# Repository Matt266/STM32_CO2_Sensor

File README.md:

# STM32_CO2_Sensor
KiCAD files and Arduino Code for SCD41 based CO2 Sensor

Most important parts:  
  -STM32L051K  
  -SCD41 (Sensor)  
  -Waveshare 1.54 inch e-Paper (V2)  
  -STLink-V2 (for programming)  

*Complete PCB with display showing measurements*

*Closer view to the PCB*

## The Hardware
The CO2 Sensor uses a Waveshare 1.54 Inch e-Paper (V2 Version) to display CO2, temperature and humidity measurements.
After creating a simple test device with an CCS811 Sensor and an Arduino Nano I wanted to create a working device.
This test device had two main issues I wanted to address: A high current consumption (50mA) and wrong measurement values
due to the cheap Sensor used.

For this I changed quite a few things. I changed the I2C-Oled Display for an e-Paper which reduces standby current consumption
but also decreases the display refresh rate. As the new more precise Sensor (SCD41) offers an one shot mode (SCD40 only got a
periodic measurement mode) the decreased refresh rate isn't a problem - measurements are only taken every few minutes.
Instead of an Arduino Board I designed a custom board. With that I could ditch the AVR MCU for a low power STM32L051. The 
PCB was designed for a STM32L011 but I underestimated the RAM and FLASH usage of code. I only got STM32L051 due to chip shortage
but would have had to "upgrade" to those anyways. I dropped the voltage level to 2.8V to make battery powering easier.

Indeed I managed to decrease the average current consumption to less than 1mA with larger spikes during measurements.

## The Software
At first I wanted to write the code with only the cmsis library but since getting all hardware components already took me months
mainly because the most important part - the MCU - wasn't available I switched to a faster method of writing code: Arduino IDE
For all features I needed there were libraries (near to) ready to use which probably cut developement time by more than a month.

I only had to do some changes to the e-Paper library (https://github.com/SSYYL/e-Paper): 
Since I didn't use the AVR I had to replace the PROGMEM calls and AVR specific libaries. In ARM based projects constant
values are stored in flash memory without special keywords anyways (linkerscript magic :D)
`
const uint8_t Font12_Table[] PROGMEM
`

There was also an AVR inline assembly call which I replaced even though it didn't seem to cause problems.

The Arduino Code itself is relatively simple: A small startup sequence configures and tests the sensor as well as
initializes the e-Paper. After that every 5 minutes a single shot measurement is taken. For simplicity I utilized
the busy waiting that was already implemented in the CO2-Library while waiting for the measurement data.
After recieving the data strings are formatted for printing them on the e-Paper. The red, yellow and green LEDs
are switched on/off based on CO2 threshold values. After displaying the new data on the display low power sleep 
is entered for 5min before taking the next measurement. Averaging algorithms are not needed as the Sensor itself
uses a sophisticated algorithm to calculate the CO2-ppm-value.

## The Problems
Sadly in DIY projects things can go wrong and some things went wrong in this project too.

First of all I somehow managed to mislabel the unused PINs which isn't fixed in the KiCAD files yet.
The next problem was that I couldn't get reliable connections soldering the Sensor to the PCB directly.
As the solder joints can't be seen after soldering I could never know if I all joints were good. 
After some weeks of seemingly random errors I used wires to solder the sensor to the PCB. It may not look
good or professional but at least works reliable.
The last and most expensive thing I did wrong killed the sensor and some Pins on the MCU. 
For debbuging purposes I used an STM32 evaluation board and connected to the I2C header of the PCB and
reading the serial monitor.
After finally getting a MCU I tried to test the same code with the STM32L051. I didn't turn off the serial
messages. As the standard UART on STML051 uses the same PINs as I2C on STM32L011 those were directly connected
to the sensors I2C pins. Thus sending a serial message lead to a short circuit resulting in a dead sensor and
fried PINs on the MCU.

## Future Plans
As of the state of writing the PCB is powered by a 2.8V LDO. For making it battery powered a boost converter
will be added on a seperate PCB. Also after adding the boost converter an enclosure to protect everything will
be made.

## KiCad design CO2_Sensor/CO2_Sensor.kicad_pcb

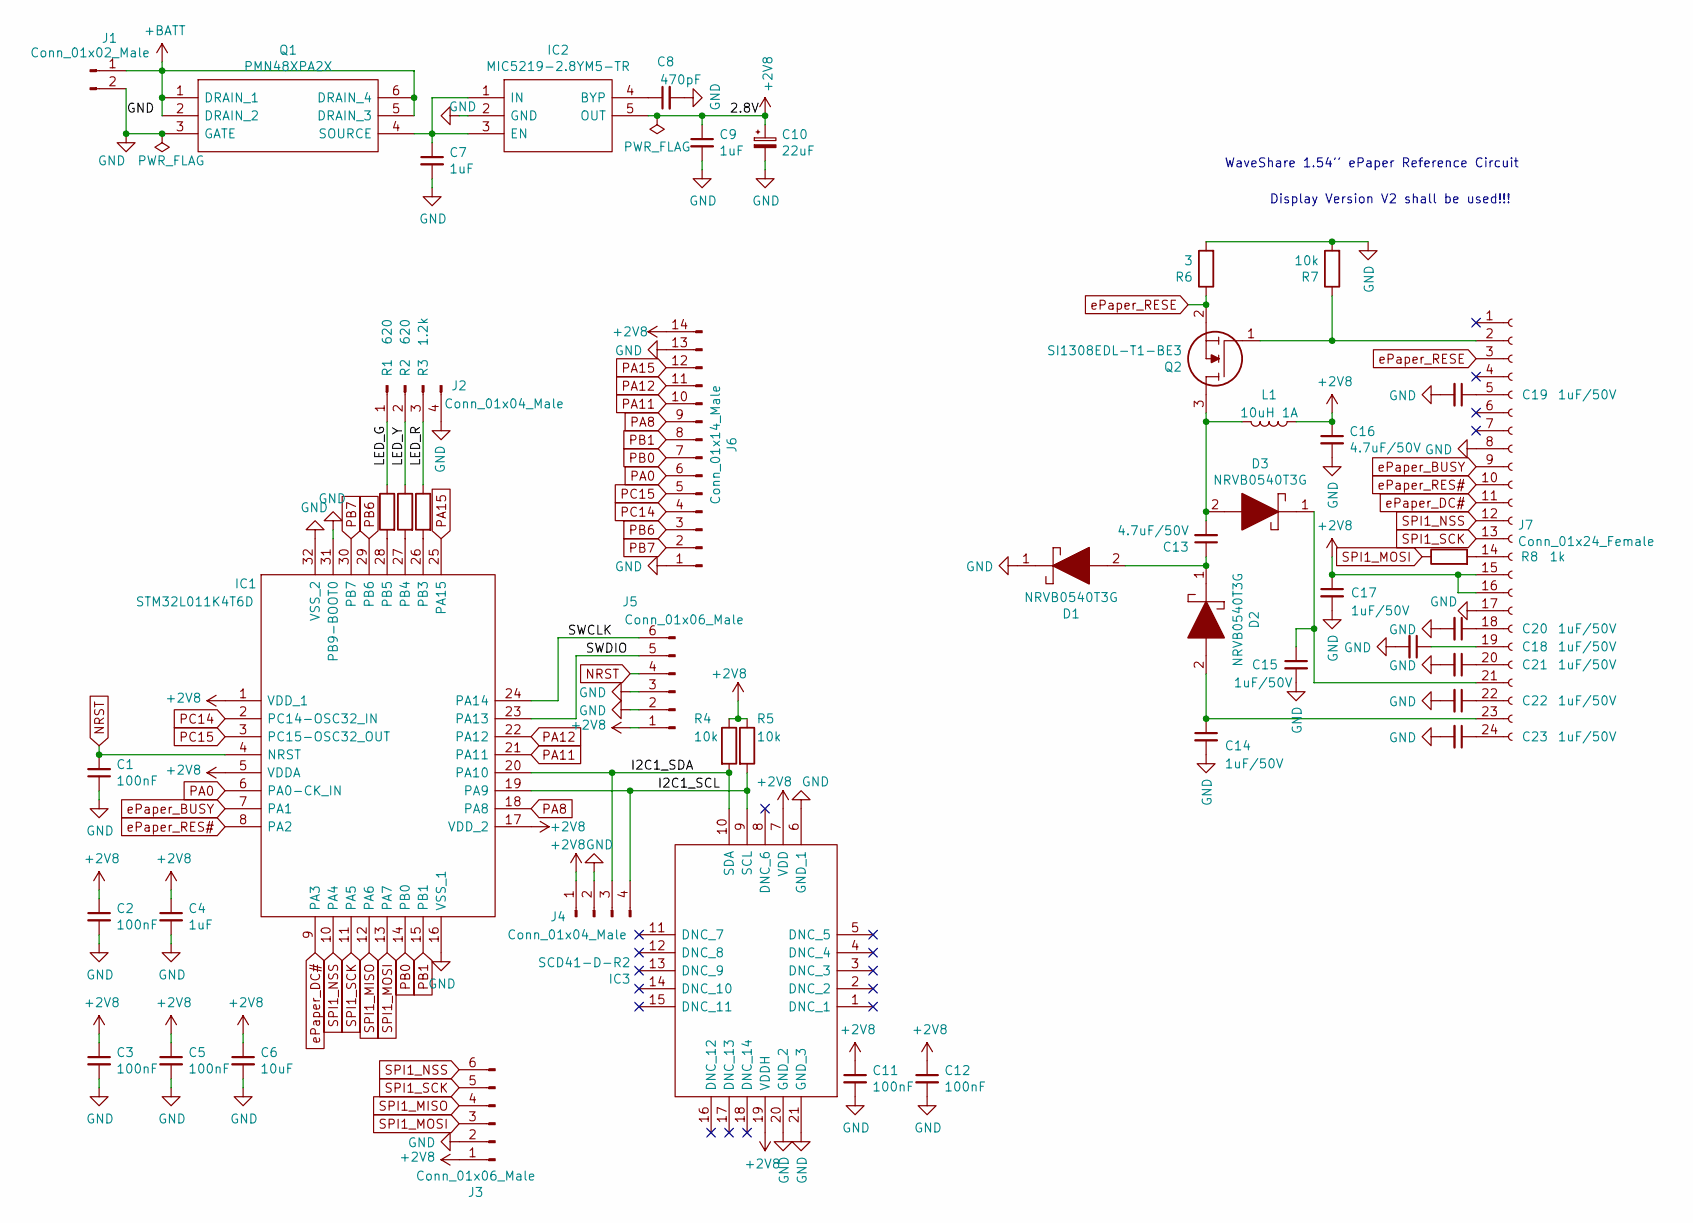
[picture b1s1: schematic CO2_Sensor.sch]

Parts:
C1, C2, C3, C5, C11, C12: 100nF; C_0805_2012Metric_Pad1.18x1.45mm_HandSolder
C4, C7, C9: 1uF; C_0805_2012Metric_Pad1.18x1.45mm_HandSolder
C6: 10uF; C_0805_2012Metric_Pad1.18x1.45mm_HandSolder
C8: 470pF; C_0805_2012Metric_Pad1.18x1.45mm_HandSolder
C10: 22uF; CP_Elec_4x5.4
C13, C16: 4.7uF/50V; C_0805_2012Metric_Pad1.18x1.45mm_HandSolder
C14, C15, C17, C18, C19, C20, C21, C22, C23: 1uF/50V; C_0805_2012Metric_Pad1.18x1.45mm_HandSolder
D1, D2, D3: NRVB0540T3G; SOD3716X135N; Mouser Part Number 863-NRVB0540T3G
IC1: STM32L011K4T6D; QFP80P900X900X160-32N; Mouser Part Number 511-STM32L011K4T6D
IC2: MIC5219-2.8YM5-TR; SOT95P280X145-5N; Mouser Part Number 998-MIC5219-2.8YM5TR
IC3: SCD41-D-R2; SCD41DR2; Mouser Part Number 403-SCD41-D-R2
J1: Conn_01x02_Male; PinSocket_1x02_P2.54mm_Vertical
J2, J4: Conn_01x04_Male; PinSocket_1x04_P2.54mm_Vertical
J3, J5: Conn_01x06_Male; PinSocket_1x06_P2.54mm_Vertical
J6: Conn_01x14_Male; PinSocket_1x14_P2.54mm_Vertical
J7: Conn_01x24_Female; TE_2-1734839-4_1x24-1MP_P0.5mm_Horizontal
L1: 10uH 1A; L_0805_2012Metric_Pad1.05x1.20mm_HandSolder
Q1: PMN48XPA2X; SOT95P275X110-6N; Mouser Part Number 771-PMN48XPA2X
Q2: SI1308EDL-T1-BE3; SOT65P210X110-3N; Mouser Part Number 78-SI1308EDL-T1-BE3
R1, R2: 620; R_0805_2012Metric_Pad1.20x1.40mm_HandSolder
R3: 1.2k; R_0805_2012Metric_Pad1.20x1.40mm_HandSolder
R4, R5, R7: 10k; R_0805_2012Metric_Pad1.20x1.40mm_HandSolder
R6: 3; R_0805_2012Metric_Pad1.20x1.40mm_HandSolder
R8: 1k; R_0805_2012Metric_Pad1.20x1.40mm_HandSolder

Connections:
+2V8: C2.1, C3.1, C4.1, C5.1, C6.1, C9.1, C10.1, C11.1, C12.1, C16.1, C17.1, IC1.1 (VDD_1), IC1.5 (VDDA), IC1.17 (VDD_2), IC2.5 (OUT), IC3.7 (VDD), IC3.19 (VDDH), J3.1, J4.1, J5.1, J6.14, J7.15, J7.16, L1.1, R4.1, R5.1
+BATT: J1.1, Q1.1 (DRAIN_1), Q1.2 (DRAIN_2), Q1.5 (DRAIN_3), Q1.6 (DRAIN_4)
/I2C1_SCL: IC1.19 (PA9), IC3.9 (SCL), J4.4, R5.2
/I2C1_SDA: IC1.20 (PA10), IC3.10 (SDA), J4.3, R4.2
/LED_G: J2.1, R1.1
/LED_R: J2.3, R3.1
/LED_Y: J2.2, R2.1
/SWCLK: IC1.24 (PA14), J5.6
/SWDIO: IC1.23 (PA13), J5.5
GND: C1.1, C2.2, C3.2, C4.2, C5.2, C6.2, C7.2, C8.2, C9.2, C10.2, C11.2, C12.2, C14.2, C15.2, C16.2, C17.2, C18.2, C19.2, C20.2, C21.2, C22.2, C23.2, D1.1, IC1.16 (VSS_1), IC1.31 (PB9-BOOT0), IC1.32 (VSS_2), IC2.2 (GND), IC3.6 (GND_1), IC3.20 (GND_2), IC3.21 (GND_3), J1.2, J2.4, J3.2, J4.2, J5.2, J5.3, J6.1, J6.13, J7.8, J7.17, Q1.3 (GATE), R6.2, R7.2
NRST: C1.2, IC1.4 (NRST), J5.4
unnamed: C7.1, IC2.1 (IN), IC2.3 (EN), Q1.4 (SOURCE)
unnamed: C8.1, IC2.4 (BYP)
unnamed: C13.1, D1.2, D2.1
unnamed: C13.2, D3.2, L1.2, Q2.3
unnamed: C14.1, D2.2, J7.23
unnamed: C15.1, D3.1, J7.21
unnamed: C18.1, J7.19
unnamed: C19.1, J7.5
unnamed: C20.1, J7.18
unnamed: C21.1, J7.20
unnamed: C22.1, J7.22
unnamed: C23.1, J7.24
unnamed: IC1.26 (PB3), R3.2
unnamed: IC1.27 (PB4), R2.2
unnamed: IC1.28 (PB5), R1.2
unnamed: J7.2, Q2.1, R7.1
unnamed: J7.14, R8.2
PA0: IC1.6 (PA0-CK_IN), J6.6
PA8: IC1.18 (PA8), J6.9
PA11: IC1.21 (PA11), J6.10
PA12: IC1.22 (PA12), J6.11
PA15: IC1.25 (PA15), J6.12
PB0: IC1.14 (PB0), J6.7
PB1: IC1.15 (PB1), J6.8
PB6: IC1.29 (PB6), J6.3
PB7: IC1.30 (PB7), J6.2
PC14: IC1.2 (PC14-OSC32_IN), J6.4
PC15: IC1.3 (PC15-OSC32_OUT), J6.5
SPI1_MISO: IC1.12 (PA6), J3.4
SPI1_MOSI: IC1.13 (PA7), J3.3, R8.1
SPI1_NSS: IC1.10 (PA4), J3.6, J7.12
SPI1_SCK: IC1.11 (PA5), J3.5, J7.13
ePaper_BUSY: IC1.7 (PA1), J7.9
ePaper_DC#: IC1.9 (PA3), J7.11
ePaper_RES#: IC1.8 (PA2), J7.10
ePaper_RESE: J7.3, Q2.2, R6.1

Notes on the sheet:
WaveShare 1.54'' ePaper Reference Circuit
Display Version V2 shall be used!!!

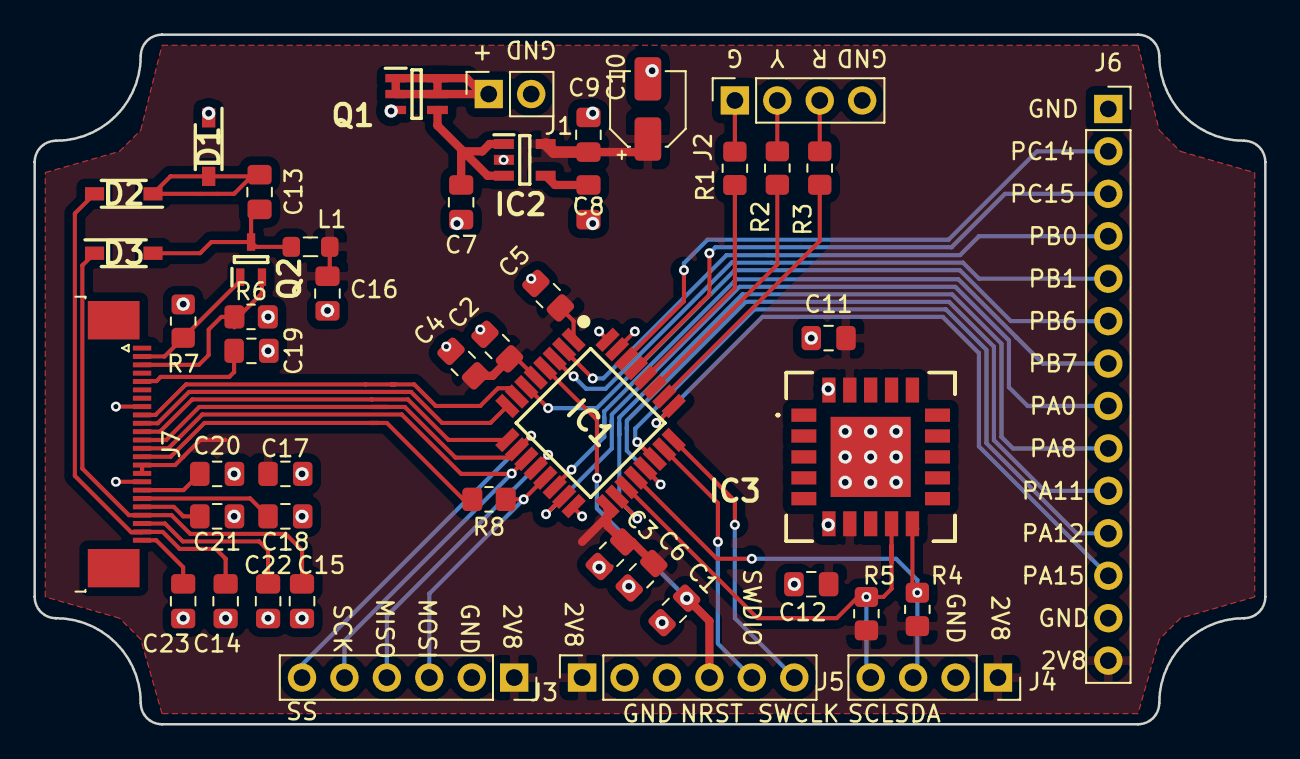
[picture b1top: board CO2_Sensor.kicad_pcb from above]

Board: 2 copper layers, 73.7 x 41.3 mm, 47 parts (0 on the bottom side), 47 nets.

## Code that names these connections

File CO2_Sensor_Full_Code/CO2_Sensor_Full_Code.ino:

#include <SPI.h>
#include <SensirionCore.h>
#include <SensirionI2CScd4x.h>
#include <Wire.h>
#include "epdpaint.h"
#include "epd1in54_V2.h"
#include <stdio.h>
#include "STM32LowPower.h"

Epd epd;
unsigned char image[1024];
Paint paint(image, 0, 0);

#define COLORED     0
#define UNCOLORED   1

#define I2C1_SCL_PIN PB6
#define I2C1_SDA_PIN PB7
#define LEGACY_PIN_1 PA10
#define LEGACY_PIN_0 PA9
#define LED_R PB3
#define LED_Y PB4
#define LED_G PB5

#define YELLOW_VALUE 800
#define RED_VALUE 1400

SensirionI2CScd4x scd4x;
uint16_t sensorStatus = 0;
uint16_t co2_value;
float temperature;
float humidity;

char co2_msg[25] = {0};
char hum_msg[25] = {0};
char temp_msg[25] = {0};
 
void setup()
{
  pinMode(LEGACY_PIN_0,INPUT);
  pinMode(LEGACY_PIN_1,INPUT);
  pinMode(LED_R,OUTPUT);
  pinMode(LED_Y,OUTPUT);
  pinMode(LED_G,OUTPUT);
  Wire.setSCL(I2C1_SCL_PIN);
  Wire.setSDA(I2C1_SDA_PIN);
  SPI.setSCLK(PA5);
  SPI.setMISO(PA6);
  SPI.setMOSI(PA7);
  LowPower.begin();
  epd.LDirInit();
  epd.Clear();
  paint.SetWidth(200);
  paint.SetHeight(24);

  Wire.begin();
  scd4x.begin(Wire);
  delay(1000);//Sensor startup to idle
  scd4x.stopPeriodicMeasurement();

  scd4x.performSelfTest(sensorStatus);
  paint.Clear(UNCOLORED);
  if(sensorStatus){
    paint.DrawStringAt(0,0,"Sensor defekt", &Font20, COLORED);
  }
  else{
    paint.DrawStringAt(0,0,"Sensor intakt", &Font20, COLORED);
  }
  epd.SetFrameMemory(paint.GetImage(), 10, 96, paint.GetWidth(), paint.GetHeight());
  epd.DisplayFrame();
  
 //scd4x.startPeriodicMeasurement();

 //discard first two measurements
 scd4x.measureSingleShot();
 scd4x.measureSingleShot();

  paint.Clear(UNCOLORED);
  epd.SetFrameMemory(paint.GetImage(), 10, 96, paint.GetWidth(), paint.GetHeight());
  epd.DisplayFrame();
}

void loop()
{
  scd4x.measureSingleShot();
  //delay(5500);
  scd4x.readMeasurement(co2_value, temperature, humidity);
  sprintf(co2_msg, "CO2: %dppm",co2_value);
  sprintf(hum_msg, "Hum: %d,%d%%",(uint16_t)humidity,(uint16_t)(humidity*100)-(((uint16_t)humidity)*100));
  sprintf(temp_msg, "Temp: %d,%dC",(uint16_t)temperature,(uint16_t)(temperature*100)-(((uint16_t)temperature)*100));

  if(co2_value < YELLOW_VALUE){
    digitalWrite(LED_Y, LOW);
    digitalWrite(LED_R,LOW);
    digitalWrite(LED_G, HIGH);
  } else if(co2_value < RED_VALUE){
    digitalWrite(LED_R,LOW);
    digitalWrite(LED_G, LOW);
    digitalWrite(LED_Y, HIGH);
  } else{
    digitalWrite(LED_Y,LOW);
    digitalWrite(LED_G, LOW);
    digitalWrite(LED_R, HIGH);
  }
  paint.Clear(UNCOLORED);
  paint.DrawStringAt(0,0,co2_msg, &Font20, COLORED);
  epd.SetFrameMemory(paint.GetImage(), 0, 48, paint.GetWidth(), paint.GetHeight());
  paint.Clear(UNCOLORED);
  paint.DrawStringAt(0,0,hum_msg, &Font20, COLORED);
  epd.SetFrameMemory(paint.GetImage(), 0, 96, paint.GetWidth(), paint.GetHeight());
  paint.Clear(UNCOLORED);
  paint.DrawStringAt(0,0,temp_msg, &Font20, COLORED);
  epd.SetFrameMemory(paint.GetImage(), 0, 144, paint.GetWidth(), paint.GetHeight());
  epd.DisplayFrame();

  LowPower.sleep(300000);
}

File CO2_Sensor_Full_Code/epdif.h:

/**
 *  @filename   :   epdif.h
 *  @brief      :   Header file of epdif.cpp providing EPD interface functions
 *                  Users have to implement all the functions in epdif.cpp
 *  @author     :   Yehui from Waveshare
 *
 *  Copyright (C) Waveshare     August 10 2017
 *
 * Permission is hereby granted, free of charge, to any person obtaining a copy
 * of this software and associated documnetation files (the "Software"), to deal
 * in the Software without restriction, including without limitation the rights
 * to use, copy, modify, merge, publish, distribute, sublicense, and/or sell
 * copies of the Software, and to permit persons to  whom the Software is
 * furished to do so, subject to the following conditions:
 *
 * The above copyright notice and this permission notice shall be included in
 * all copies or substantial portions of the Software.
 *
 * THE SOFTWARE IS PROVIDED "AS IS", WITHOUT WARRANTY OF ANY KIND, EXPRESS OR
 * IMPLIED, INCLUDING BUT NOT LIMITED TO THE WARRANTIES OF MERCHANTABILITY,
 * FITNESS OR A PARTICULAR PURPOSE AND NONINFRINGEMENT. IN NO EVENT SHALL THE
 * AUTHORS OR COPYRIGHT HOLDERS BE LIABLE FOR ANY CLAIM, DAMAGES OR OTHER
 * LIABILITY WHETHER IN AN ACTION OF CONTRACT, TORT OR OTHERWISE, ARISING FROM,
 * OUT OF OR IN CONNECTION WITH THE SOFTWARE OR THE USE OR OTHER DEALINGS IN
 * THE SOFTWARE.
 */

#ifndef EPDIF_H
#define EPDIF_H

#include <Arduino.h>

// Pin definition
#define RST_PIN         PA2
#define DC_PIN          PA3
#define CS_PIN          PA4
#define BUSY_PIN        PA1

class EpdIf {
public:
    EpdIf(void);
    ~EpdIf(void);

    static int  IfInit(void);
    static void DigitalWrite(int pin, int value); 
    static int  DigitalRead(int pin);
    static void DelayMs(unsigned int delaytime);
    static void SpiTransfer(unsigned char data);
};

#endif
